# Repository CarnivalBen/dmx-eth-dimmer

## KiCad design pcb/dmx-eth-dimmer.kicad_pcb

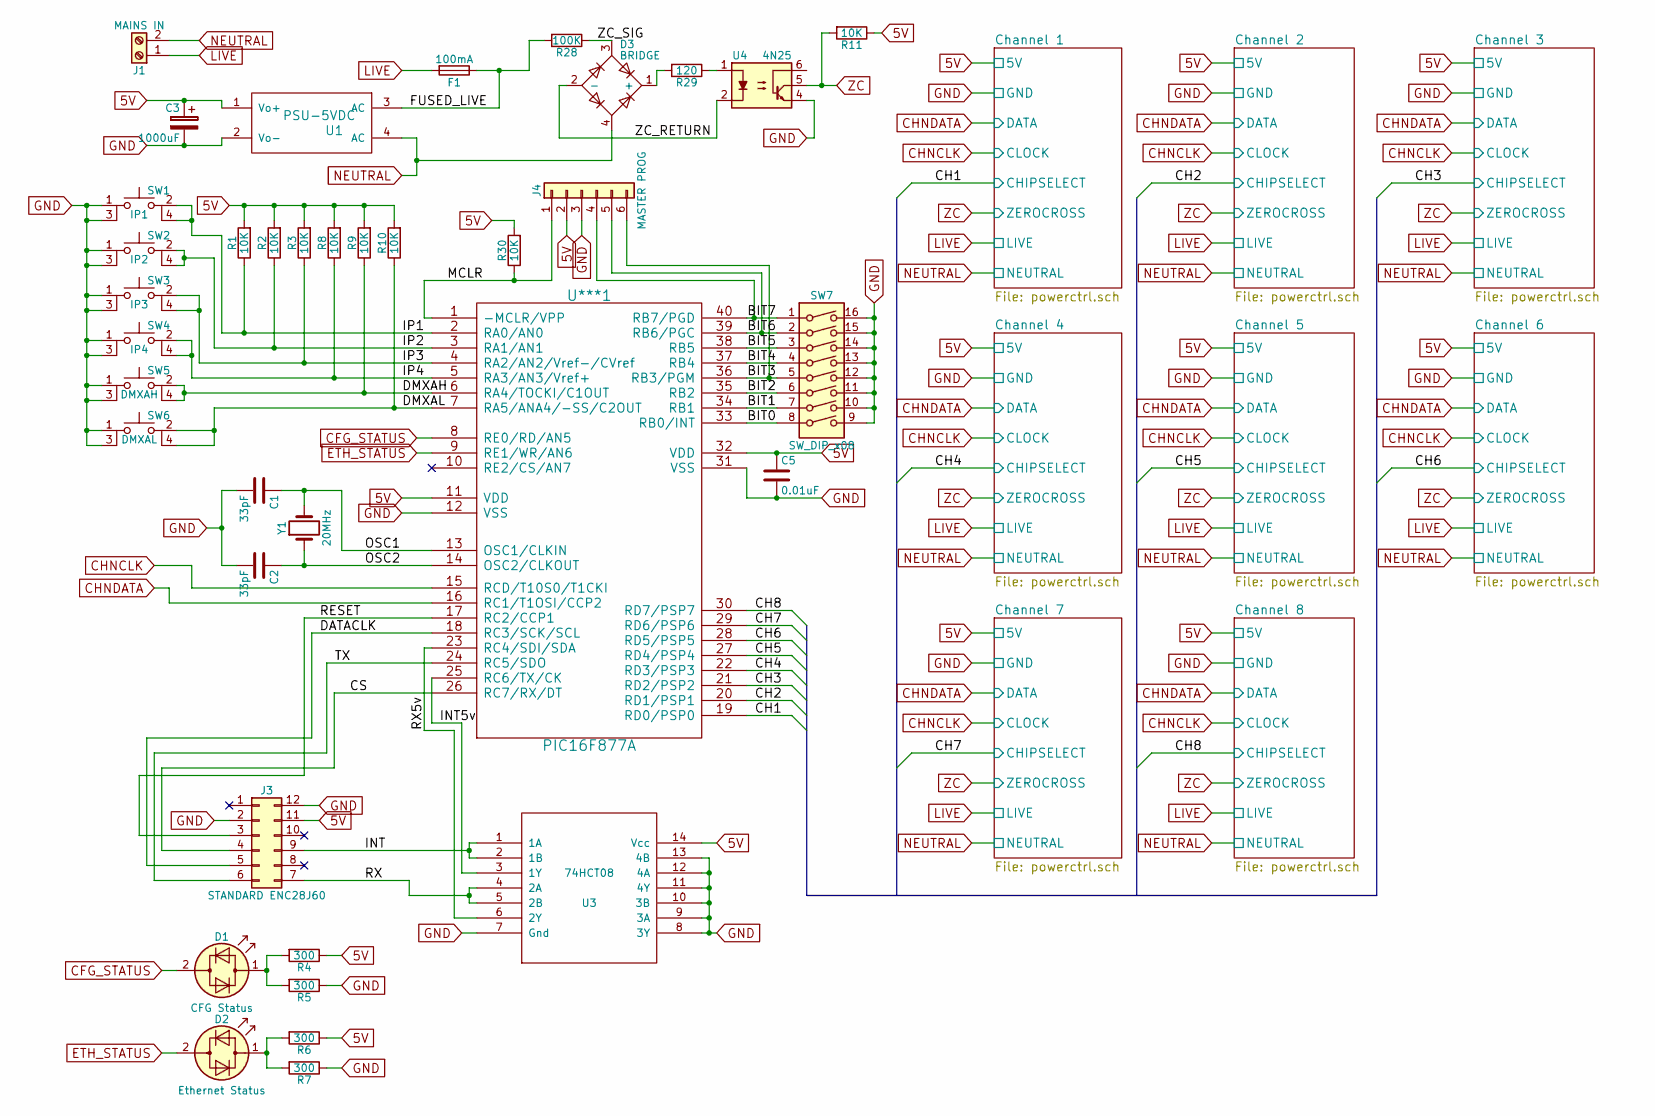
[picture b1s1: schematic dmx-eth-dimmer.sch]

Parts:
C1, C2: 33pF; C_Disc_D3.0mm_W1.6mm_P2.50mm
C3: 1000uF; CP_Radial_D10.0mm_P5.00mm
C5: 0.01uF; C_Disc_D3.0mm_W1.6mm_P2.50mm
D1: CFG Status; LED_D3.0mm
D2: Ethernet Status; LED_D3.0mm
D3: BRIDGE; Diode_Bridge_W08
F1: 100mA; Fuseholder5x20_horiz_open_inline_Type-I
J1: MAINS IN; TerminalBlock_bornier-2_P5.08mm
J3: STANDARD ENC28J60; Pin_Header_Straight_2x06_Pitch2.54mm
J4: MASTER PROG; Pin_Header_Straight_1x06_Pitch2.54mm
R1, R2, R3, R8, R9, R10, R11, R30: 10K; R_Axial_DIN0207_L6.3mm_D2.5mm_P10.16mm_Horizontal
R4, R5, R6, R7: 300; R_Axial_DIN0207_L6.3mm_D2.5mm_P10.16mm_Horizontal
R28: 100K; R_Axial_DIN0207_L6.3mm_D2.5mm_P10.16mm_Horizontal
R29: 120; R_Axial_DIN0207_L6.3mm_D2.5mm_P10.16mm_Horizontal
SW1: IP1; SW_PUSH_6mm_4pin
SW2: IP2; SW_PUSH_6mm_4pin
SW3: IP3; SW_PUSH_6mm_4pin
SW4: IP4; SW_PUSH_6mm_4pin
SW5: DMXAH; SW_PUSH_6mm_4pin
SW6: DMXAL; SW_PUSH_6mm_4pin
SW7: SW_DIP_x08; SW_DIP_x8_W7.62mm_Slide
U1: PSU-5VDC; HLK-PM01
U3: 74HCT08; DIP-14_W7.62mm
U4: 4N25; DIP-6_W7.62mm
U***1: PIC16F877A; DIP-40_W15.24mm
Y1: 20MHz; Crystal_HC50_Vertical

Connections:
5V: C3.1, C5.1, J3.11, J4.2, R1.2, R2.2, R3.2, R4.1, R6.1, R8.2, R9.2, R10.2, R11.1, R30.2, U1.1 (Vo+), U3.14 (Vcc), U***1.11 (VDD), U***1.32 (VDD); also elsewhere on the board
/BIT0: SW7.8, U***1.33 (RB0/INT)
/BIT1: SW7.7, U***1.34 (RB1)
/BIT2: SW7.6, U***1.35 (RB2)
/BIT3: J4.6, SW7.5, U***1.36 (RB3/PGM)
/BIT4: SW7.4, U***1.37 (RB4)
/BIT5: SW7.3, U***1.38 (RB5)
/BIT6: J4.5, SW7.2, U***1.39 (RB6/PGC)
/BIT7: J4.4, SW7.1, U***1.40 (RB7/PGD)
/CH1: U***1.19 (RD0/PSP0); also elsewhere on the board
/CH2: U***1.20 (RD1/PSP1); also elsewhere on the board
/CH3: U***1.21 (RD2/PSP2); also elsewhere on the board
/CH4: U***1.22 (RD3/PSP3); also elsewhere on the board
/CH5: U***1.27 (RD4/PSP4); also elsewhere on the board
/CH6: U***1.28 (RD5/PSP5); also elsewhere on the board
/CH7: U***1.29 (RD6/PSP6); also elsewhere on the board
/CH8: U***1.30 (RD7/PSP7); also elsewhere on the board
/CS: J3.4, U***1.26 (RC7/RX/DT)
/DATACLK: J3.5, U***1.18 (RC3/SCK/SCL)
/DMXAH: R9.1, SW5.2, SW5.4, U***1.6 (RA4/TOCKI/C1OUT)
/DMXAL: R10.1, SW6.2, SW6.4, U***1.7 (RA5/ANA4/-SS/C2OUT)
/FUSED_LIVE: F1.1, R28.2, U1.3 (AC)
/INT: J3.9, U3.1 (1A), U3.2 (1B)
/INT5v: U3.3 (1Y), U***1.25 (RC6/TX/CK)
/IP1: R1.1, SW1.2, SW1.4, U***1.2 (RA0/AN0)
/IP2: R2.1, SW2.2, SW2.4, U***1.3 (RA1/AN1)
/IP3: R3.1, SW3.2, SW3.4, U***1.4 (RA2/AN2/Vref-/CVref)
/IP4: R8.1, SW4.2, SW4.4, U***1.5 (RA3/AN3/Vref+)
/MCLR: J4.1, R30.1, U***1.1 (-MCLR/VPP)
/OSC1: C1.1, U***1.13 (OSC1/CLKIN), Y1.2
/OSC2: C2.1, U***1.14 (OSC2/CLKOUT), Y1.1
/RESET: J3.3, U***1.17 (RC2/CCP1)
/RX: J3.7, U3.4 (2A), U3.5 (2B)
/RX5v: U3.6 (2Y), U***1.23 (RC4/SDI/SDA)
/TX: J3.6, U***1.24 (RC5/SDO)
/ZC_RETURN: D3.2 (-), U4.2
/ZC_SIG: D3.3, R28.1
CFG_STATUS: D1.2 (AK), U***1.8 (RE0/RD/AN5)
CHNCLK: U***1.15 (RCD/T10S0/T1CKI); also elsewhere on the board
CHNDATA: U***1.16 (RC1/T1OSI/CCP2); also elsewhere on the board
ETH_STATUS: D2.2 (AK), U***1.9 (RE1/WR/AN6)
GND: C1.2, C2.2, C3.2, C5.2, J3.2, J3.12, J4.3, R5.1, R7.1, SW1.1, SW1.3, SW2.1, SW2.3, SW3.1, SW3.3, SW4.1, SW4.3, SW5.1, SW5.3, SW6.1, SW6.3, SW7.9, SW7.10, SW7.11, SW7.12, SW7.13, SW7.14, SW7.15, SW7.16, U1.2 (Vo-), U3.7 (Gnd), U3.8 (3Y), U3.9 (3A), U3.10 (3B), U3.11 (4Y), U3.12 (4A), U3.13 (4B), U4.4, U***1.12 (VSS), U***1.31 (VSS); also elsewhere on the board
LIVE: F1.2, J1.1; also elsewhere on the board
NEUTRAL: D3.4, J1.2, U1.4 (AC); also elsewhere on the board
unnamed: D1.1 (KA), R4.2, R5.2
unnamed: D2.1 (KA), R6.2, R7.2
unnamed: D3.1 (+), R29.2
unnamed: R29.1, U4.1
ZC: R11.2, U4.5; also elsewhere on the board

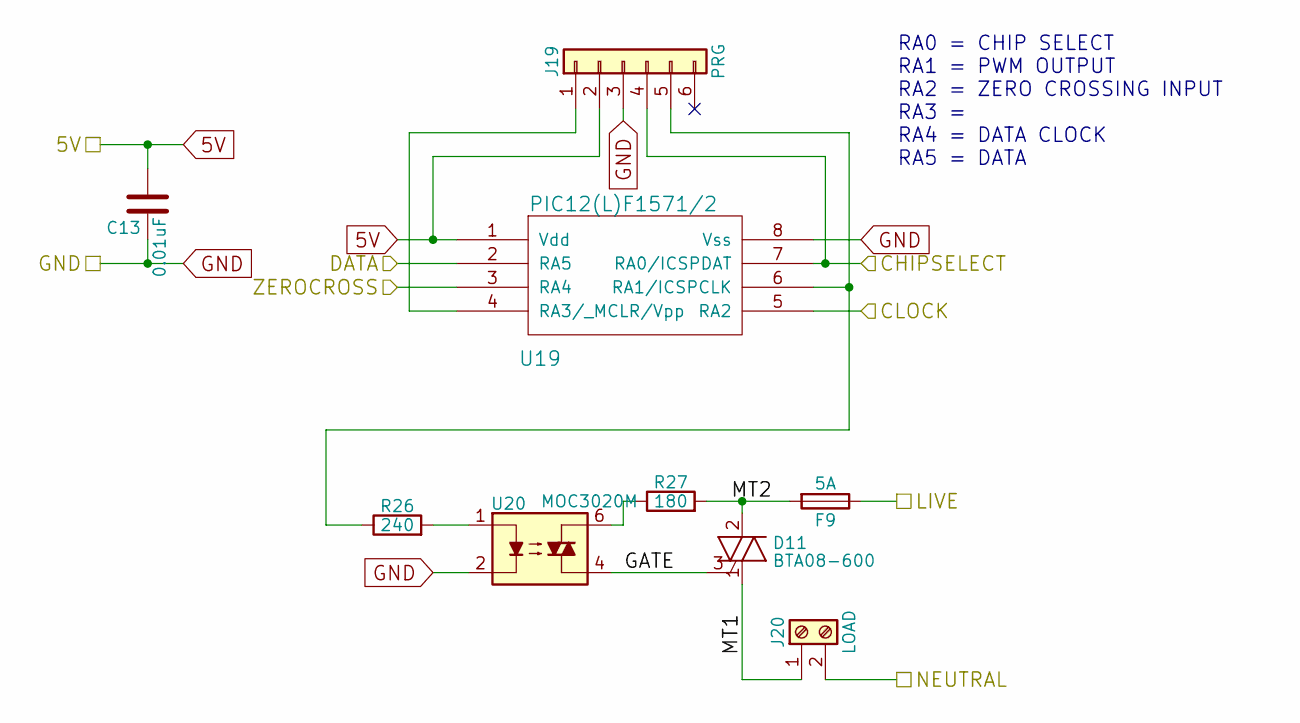
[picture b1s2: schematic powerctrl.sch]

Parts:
C6: 0.01uF; C_Disc_D3.0mm_W1.6mm_P2.50mm
D4: BTA08-600; TO-220-3_Vertical
F2: 5A; Fuseholder5x20_horiz_open_inline_Type-I
J5: PRG; Pin_Header_Straight_1x06_Pitch2.54mm
J6: LOAD; TerminalBlock_bornier-2_P5.08mm
R12: 240; R_Axial_DIN0207_L6.3mm_D2.5mm_P10.16mm_Horizontal
R13: 180; R_Axial_DIN0207_L6.3mm_D2.5mm_P10.16mm_Horizontal
U5: PIC12(L)F1571/2; DIP-8_W7.62mm
U6: MOC3020M; DIP-6_W7.62mm

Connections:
5V: C6.2, J5.2, U5.1 (Vdd); also elsewhere on the board
/CH1: J5.4, U5.7 (RA0/ICSPDAT); also elsewhere on the board
/Channel 1/GATE: D4.3 (G), U6.4
/Channel 1/MT1: D4.1 (MT1), J6.1
/Channel 1/MT2: D4.2 (MT2), F2.2, R13.2
CHNCLK: U5.5 (RA2); also elsewhere on the board
CHNDATA: U5.2 (RA5); also elsewhere on the board
GND: C6.1, J5.3, U5.8 (Vss), U6.2; also elsewhere on the board
LIVE: F2.1; also elsewhere on the board
NEUTRAL: J6.2; also elsewhere on the board
unnamed: J5.1, U5.4 (RA3/_MCLR/Vpp)
unnamed: J5.5, R12.1, U5.6 (RA1/ICSPCLK)
unnamed: R12.2, U6.1
unnamed: R13.1, U6.6
ZC: U5.3 (RA4); also elsewhere on the board

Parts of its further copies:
C7, C8, C9, C10, C11, C12, C13: 0.01uF; C_Disc_D3.0mm_W1.6mm_P2.50mm
D5, D6, D7, D8, D9, D10, D11: BTA08-600; TO-220-3_Vertical
F3, F4, F5, F6, F7, F8, F9: 5A; Fuseholder5x20_horiz_open_inline_Type-I
J7, J9, J11, J13, J15, J17, J19: PRG; Pin_Header_Straight_1x06_Pitch2.54mm
J8, J10, J12, J14, J16, J18, J20: LOAD; TerminalBlock_bornier-2_P5.08mm
R14, R16, R18, R20, R22, R24, R26: 240; R_Axial_DIN0207_L6.3mm_D2.5mm_P10.16mm_Horizontal
R15, R17, R19, R21, R23, R25, R27: 180; R_Axial_DIN0207_L6.3mm_D2.5mm_P10.16mm_Horizontal
U7, U9, U11, U13, U15, U17, U19: PIC12(L)F1571/2; DIP-8_W7.62mm
U8, U10, U12, U14, U16, U18, U20: MOC3020M; DIP-6_W7.62mm

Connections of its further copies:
5V: C7.2, C8.2, C9.2, C10.2, C11.2, C12.2, C13.2, J7.2, J9.2, J11.2, J13.2, J15.2, J17.2, J19.2, U7.1 (Vdd), U9.1 (Vdd), U11.1 (Vdd), U13.1 (Vdd), U15.1 (Vdd), U17.1 (Vdd), U19.1 (Vdd); also elsewhere on the board
/CH2: J7.4, U7.7 (RA0/ICSPDAT); also elsewhere on the board
/CH3: J9.4, U9.7 (RA0/ICSPDAT); also elsewhere on the board
/CH4: J11.4, U11.7 (RA0/ICSPDAT); also elsewhere on the board
/CH5: J13.4, U13.7 (RA0/ICSPDAT); also elsewhere on the board
/CH6: J15.4, U15.7 (RA0/ICSPDAT); also elsewhere on the board
/CH7: J17.4, U17.7 (RA0/ICSPDAT); also elsewhere on the board
/CH8: J19.4, U19.7 (RA0/ICSPDAT); also elsewhere on the board
/Channel 2/GATE: D5.3 (G), U8.4
/Channel 2/MT1: D5.1 (MT1), J8.1
/Channel 2/MT2: D5.2 (MT2), F3.2, R15.2
/Channel 3/GATE: D6.3 (G), U10.4
/Channel 3/MT1: D6.1 (MT1), J10.1
/Channel 3/MT2: D6.2 (MT2), F4.2, R17.2
/Channel 4/GATE: D7.3 (G), U12.4
/Channel 4/MT1: D7.1 (MT1), J12.1
/Channel 4/MT2: D7.2 (MT2), F5.2, R19.2
/Channel 5/GATE: D8.3 (G), U14.4
/Channel 5/MT1: D8.1 (MT1), J14.1
/Channel 5/MT2: D8.2 (MT2), F6.2, R21.2
/Channel 6/GATE: D9.3 (G), U16.4
/Channel 6/MT1: D9.1 (MT1), J16.1
/Channel 6/MT2: D9.2 (MT2), F7.2, R23.2
/Channel 7/GATE: D10.3 (G), U18.4
/Channel 7/MT1: D10.1 (MT1), J18.1
/Channel 7/MT2: D10.2 (MT2), F8.2, R25.2
/Channel 8/GATE: D11.3 (G), U20.4
/Channel 8/MT1: D11.1 (MT1), J20.1
/Channel 8/MT2: D11.2 (MT2), F9.2, R27.2
CHNCLK: U7.5 (RA2), U9.5 (RA2), U11.5 (RA2), U13.5 (RA2), U15.5 (RA2), U17.5 (RA2), U19.5 (RA2); also elsewhere on the board
CHNDATA: U7.2 (RA5), U9.2 (RA5), U11.2 (RA5), U13.2 (RA5), U15.2 (RA5), U17.2 (RA5), U19.2 (RA5); also elsewhere on the board
GND: C7.1, C8.1, C9.1, C10.1, C11.1, C12.1, C13.1, J7.3, J9.3, J11.3, J13.3, J15.3, J17.3, J19.3, U7.8 (Vss), U8.2, U9.8 (Vss), U10.2, U11.8 (Vss), U12.2, U13.8 (Vss), U14.2, U15.8 (Vss), U16.2, U17.8 (Vss), U18.2, U19.8 (Vss), U20.2; also elsewhere on the board
LIVE: F3.1, F4.1, F5.1, F6.1, F7.1, F8.1, F9.1; also elsewhere on the board
NEUTRAL: J8.2, J10.2, J12.2, J14.2, J16.2, J18.2, J20.2; also elsewhere on the board
unnamed: J7.1, U7.4 (RA3/_MCLR/Vpp)
unnamed: J7.5, R14.1, U7.6 (RA1/ICSPCLK)
unnamed: J9.1, U9.4 (RA3/_MCLR/Vpp)
unnamed: J9.5, R16.1, U9.6 (RA1/ICSPCLK)
unnamed: J11.1, U11.4 (RA3/_MCLR/Vpp)
unnamed: J11.5, R18.1, U11.6 (RA1/ICSPCLK)
unnamed: J13.1, U13.4 (RA3/_MCLR/Vpp)
unnamed: J13.5, R20.1, U13.6 (RA1/ICSPCLK)
unnamed: J15.1, U15.4 (RA3/_MCLR/Vpp)
unnamed: J15.5, R22.1, U15.6 (RA1/ICSPCLK)
unnamed: J17.1, U17.4 (RA3/_MCLR/Vpp)
unnamed: J17.5, R24.1, U17.6 (RA1/ICSPCLK)
unnamed: J19.1, U19.4 (RA3/_MCLR/Vpp)
unnamed: J19.5, R26.1, U19.6 (RA1/ICSPCLK)
unnamed: R14.2, U8.1
unnamed: R15.1, U8.6
unnamed: R16.2, U10.1
unnamed: R17.1, U10.6
unnamed: R18.2, U12.1
unnamed: R19.1, U12.6
unnamed: R20.2, U14.1
unnamed: R21.1, U14.6
unnamed: R22.2, U16.1
unnamed: R23.1, U16.6
unnamed: R24.2, U18.1
unnamed: R25.1, U18.6
unnamed: R26.2, U20.1
unnamed: R27.1, U20.6
ZC: U7.3 (RA4), U9.3 (RA4), U11.3 (RA4), U13.3 (RA4), U15.3 (RA4), U17.3 (RA4), U19.3 (RA4); also elsewhere on the board

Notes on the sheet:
RA0 = CHIP SELECT RA1 = PWM OUTPUT RA2 = ZERO CROSSING INPUT RA3 = RA4 = DATA CLOCK RA5 = DATA

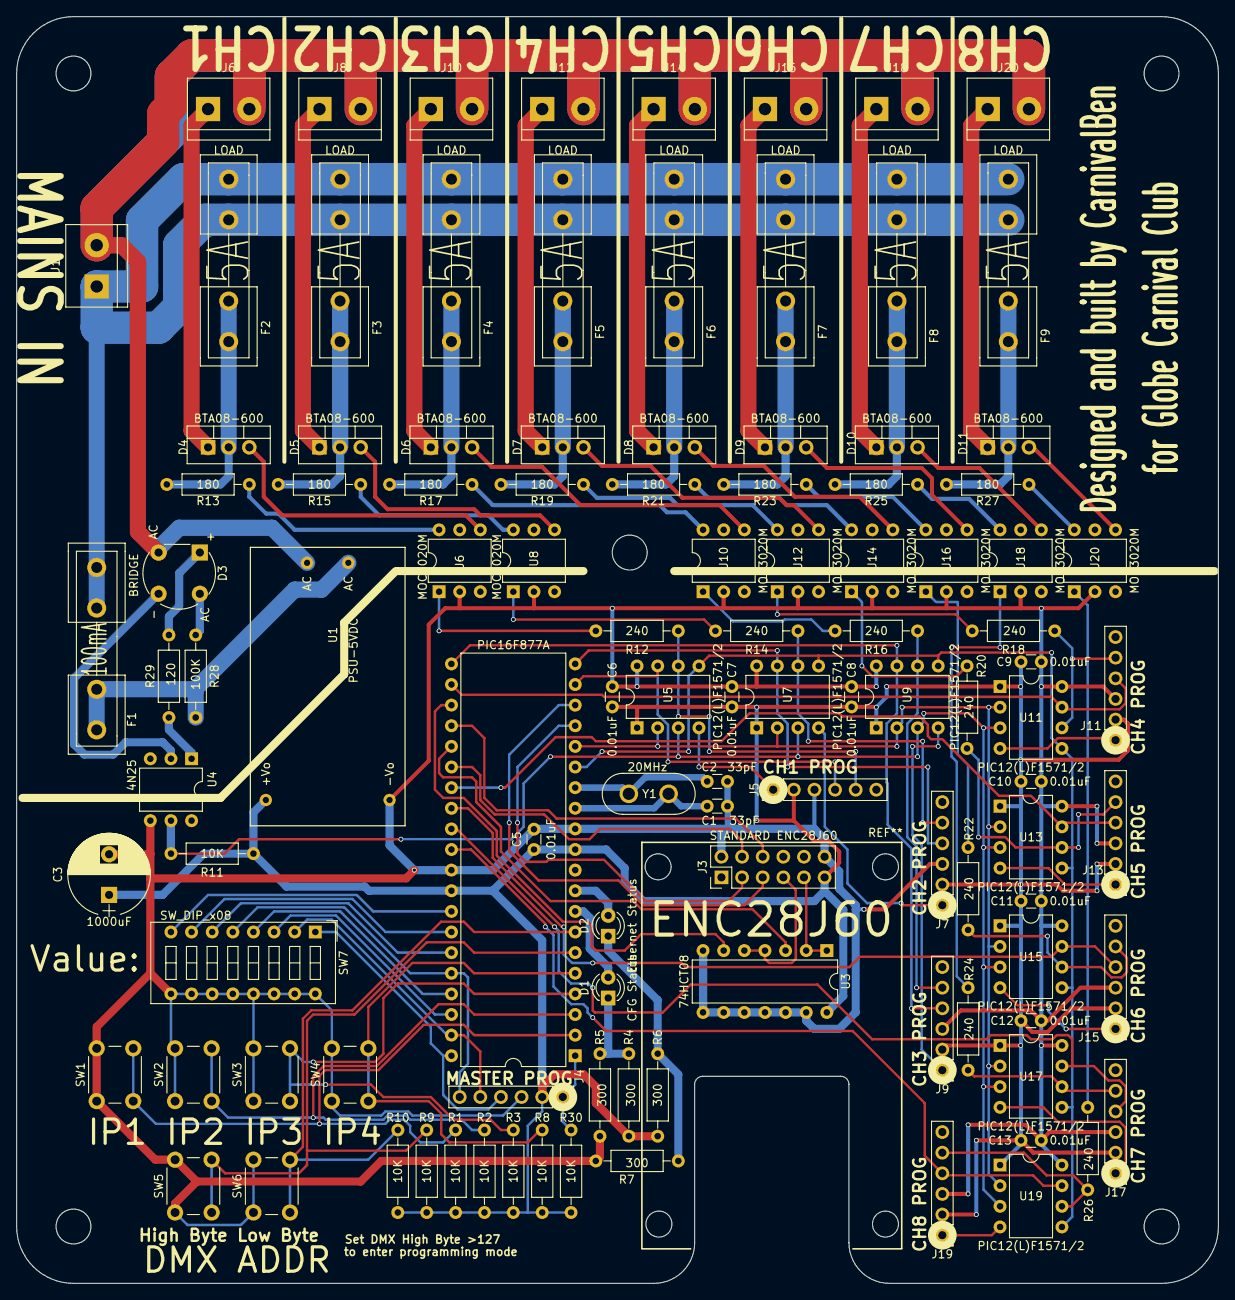
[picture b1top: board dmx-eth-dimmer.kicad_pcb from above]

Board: 2 copper layers, 148.0 x 156.0 mm, 109 parts (0 on the bottom side), 105 nets.

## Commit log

2018-06-18 Added dmx-eth-rx project.
2018-06-18 Update to PCB
2018-06-26 Updated PCB
2018-07-29 PWM1/TMR1 version
2018-07-30 Final version of dmx/ethernet controller board.
2018-08-15 New PCB Layout
2018-09-09 Added Gerbers and watchdog
2018-09-12 Fixed glitching nodes.
